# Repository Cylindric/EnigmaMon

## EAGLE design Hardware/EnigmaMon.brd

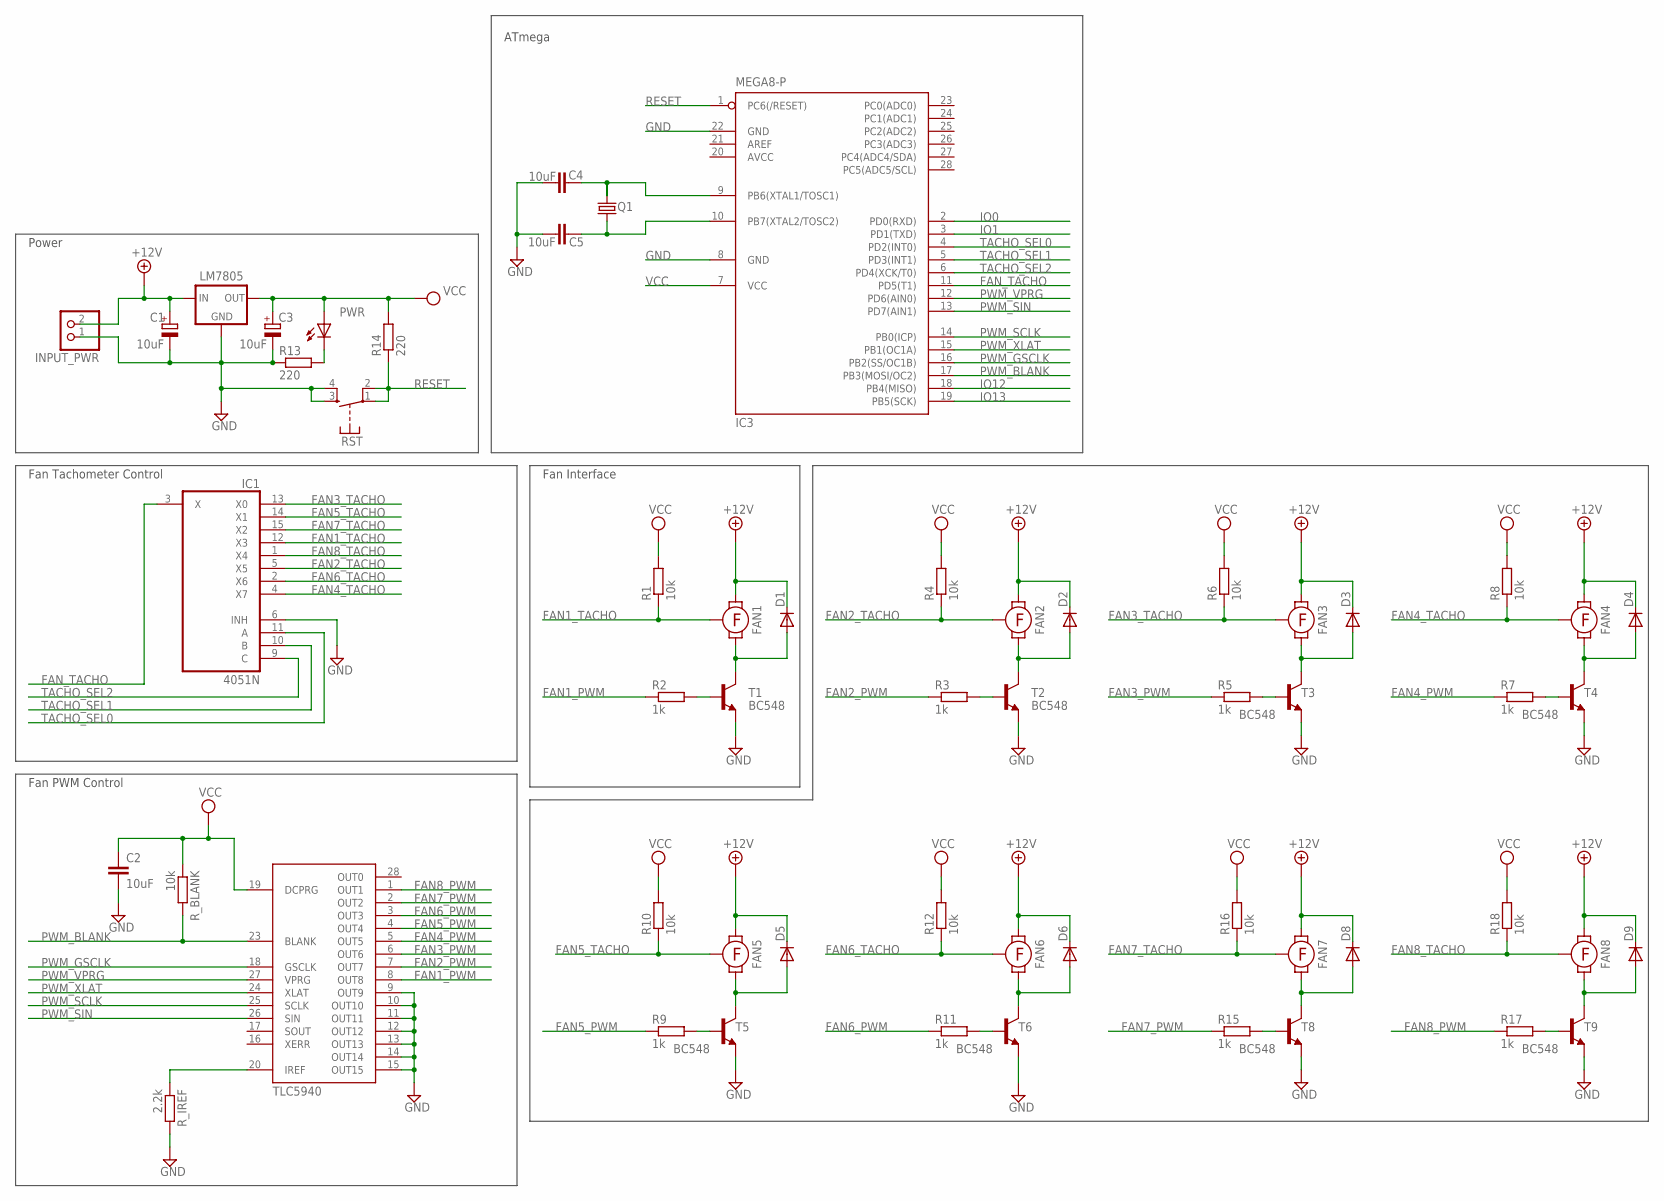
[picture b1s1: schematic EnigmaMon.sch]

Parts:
C1, C3: 10uF; E2,5-6
C2, C4, C5: 10uF; C025-025X050
D1, D2, D3, D4, D5, D6, D8, D9: DIODE-D-5; D-5
FAN1, FAN2, FAN3, FAN4, FAN5, FAN6, FAN7, FAN8: FAN; FAN_HEADER
IC1: 4051N; DIL16
IC2: TLC5940; DIL28-3
IC3: MEGA8-P; DIL28-3
INPUT_PWR: PINHD-1X2; 1X02
LM7805: 78XXL
PWR: LED3MM
Q1: CRYSTALHC49S; HC49/S
R1, R4, R6, R8, R10, R12, R16, R18: 10k; 0204/5
R2, R3, R5, R7, R9, R11, R15, R17: 1k; 0204/5
R13, R14: 220; 0204/7
RST: DTS6
R_BLANK: 10k; 0204/7
R_IREF: 2.2k; 0204/7
T1, T2, T3, T4, T5, T6, T8, T9: BC548; TO92

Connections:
+12V: C1.+, D1.C, D2.C, D3.C, D4.C, D5.C, D6.C, D8.C, D9.C, FAN1.VCC, FAN2.VCC, FAN3.VCC, FAN4.VCC, FAN5.VCC, FAN6.VCC, FAN7.VCC, FAN8.VCC, INPUT_PWR.2, LM7805.IN
AVCC: IC3.20 (AVCC)
FAN1_PWM: IC2.8 (OUT8), R2.1
FAN1_TACHO: FAN1.TACHO, IC1.12 (X3), R1.1
FAN2_PWM: IC2.7 (OUT7), R3.1
FAN2_TACHO: FAN2.TACHO, IC1.5 (X5), R4.1
FAN3_PWM: IC2.6 (OUT6), R5.1
FAN3_TACHO: FAN3.TACHO, IC1.13 (X0), R6.1
FAN4_PWM: IC2.5 (OUT5), R7.1
FAN4_TACHO: FAN4.TACHO, IC1.4 (X7), R8.1
FAN5_PWM: IC2.4 (OUT4), R9.1
FAN5_TACHO: FAN5.TACHO, IC1.14 (X1), R10.1
FAN6_PWM: IC2.3 (OUT3), R11.1
FAN6_TACHO: FAN6.TACHO, IC1.2 (X6), R12.1
FAN7_PWM: IC2.2 (OUT2), R15.1
FAN7_TACHO: FAN7.TACHO, IC1.15 (X2), R16.1
FAN8_PWM: IC2.1 (OUT1), R17.1
FAN8_TACHO: FAN8.TACHO, IC1.1 (X4), R18.1
FAN_TACHO: IC1.3 (X), IC3.11 (PD5(T1))
GND: C1.-, C2.2, C3.-, C4.1, C5.1, IC1.6 (INH), IC1.8 (GND), IC2.9 (OUT9), IC2.10 (OUT10), IC2.11 (OUT11), IC2.12 (OUT12), IC2.13 (OUT13), IC2.14 (OUT14), IC2.15 (OUT15), IC2.22 (GND), IC3.8 (GND), IC3.22 (GND), INPUT_PWR.1, LM7805.GND, R13.1, RST.3 (S), RST.4 (S), R_IREF.2, T1.1 (E), T2.1 (E), T3.1 (E), T4.1 (E), T5.1 (E), T6.1 (E), T8.1 (E), T9.1 (E)
IO0: IC3.2 (PD0(RXD))
IO1: IC3.3 (PD1(TXD))
IO12: IC3.18 (PB4(MISO))
IO13: IC3.19 (PB5(SCK))
unnamed: R3.2, T2.2 (B)
unnamed: R2.2, T1.2 (B)
unnamed: R5.2, T3.2 (B)
unnamed: R7.2, T4.2 (B)
unnamed: R9.2, T5.2 (B)
unnamed: R11.2, T6.2 (B)
unnamed: PWR.K (C), R13.2
unnamed: R15.2, T8.2 (B)
unnamed: R17.2, T9.2 (B)
unnamed: IC2.20 (IREF), R_IREF.1
unnamed: C4.2, IC3.9 (PB6(XTAL1/TOSC1)), Q1.2
unnamed: C5.2, IC3.10 (PB7(XTAL2/TOSC2)), Q1.1
unnamed: D2.A, FAN2.GND, T2.3 (C)
unnamed: D3.A, FAN3.GND, T3.3 (C)
unnamed: D4.A, FAN4.GND, T4.3 (C)
unnamed: D1.A, FAN1.GND, T1.3 (C)
unnamed: D9.A, FAN8.GND, T9.3 (C)
unnamed: D8.A, FAN7.GND, T8.3 (C)
unnamed: D6.A, FAN6.GND, T6.3 (C)
unnamed: D5.A, FAN5.GND, T5.3 (C)
PWM_BLANK: IC2.23 (BLANK), IC3.17 (PB3(MOSI/OC2)), R_BLANK.2
PWM_GSCLK: IC2.18 (GSCLK), IC3.16 (PB2(SS/OC1B))
PWM_SCLK: IC2.25 (SCLK), IC3.14 (PB0(ICP))
PWM_SIN: IC2.26 (SIN), IC3.13 (PD7(AIN1))
PWM_VPRG: IC2.27 (VPRG), IC3.12 (PD6(AIN0))
PWM_XLAT: IC2.24 (XLAT), IC3.15 (PB1(OC1A))
RESET: IC3.1 (PC6(/RESET)), R14.1, RST.1, RST.2
TACHO_SEL0: IC1.11 (A), IC3.4 (PD2(INT0))
TACHO_SEL1: IC1.10 (B), IC3.5 (PD3(INT1))
TACHO_SEL2: IC1.9 (C), IC3.6 (PD4(XCK/T0))
VCC: C2.1, C3.+, IC1.16 (VCC), IC2.19 (DCPRG), IC2.21 (VCC), IC3.7 (VCC), LM7805.OUT, PWR.A, R1.2, R4.2, R6.2, R8.2, R10.2, R12.2, R14.2, R16.2, R18.2, R_BLANK.1
VEE: IC1.7 (VEE)

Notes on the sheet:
Fan Tachometer Control
Power
Fan Interface
ATmega
Fan PWM Control

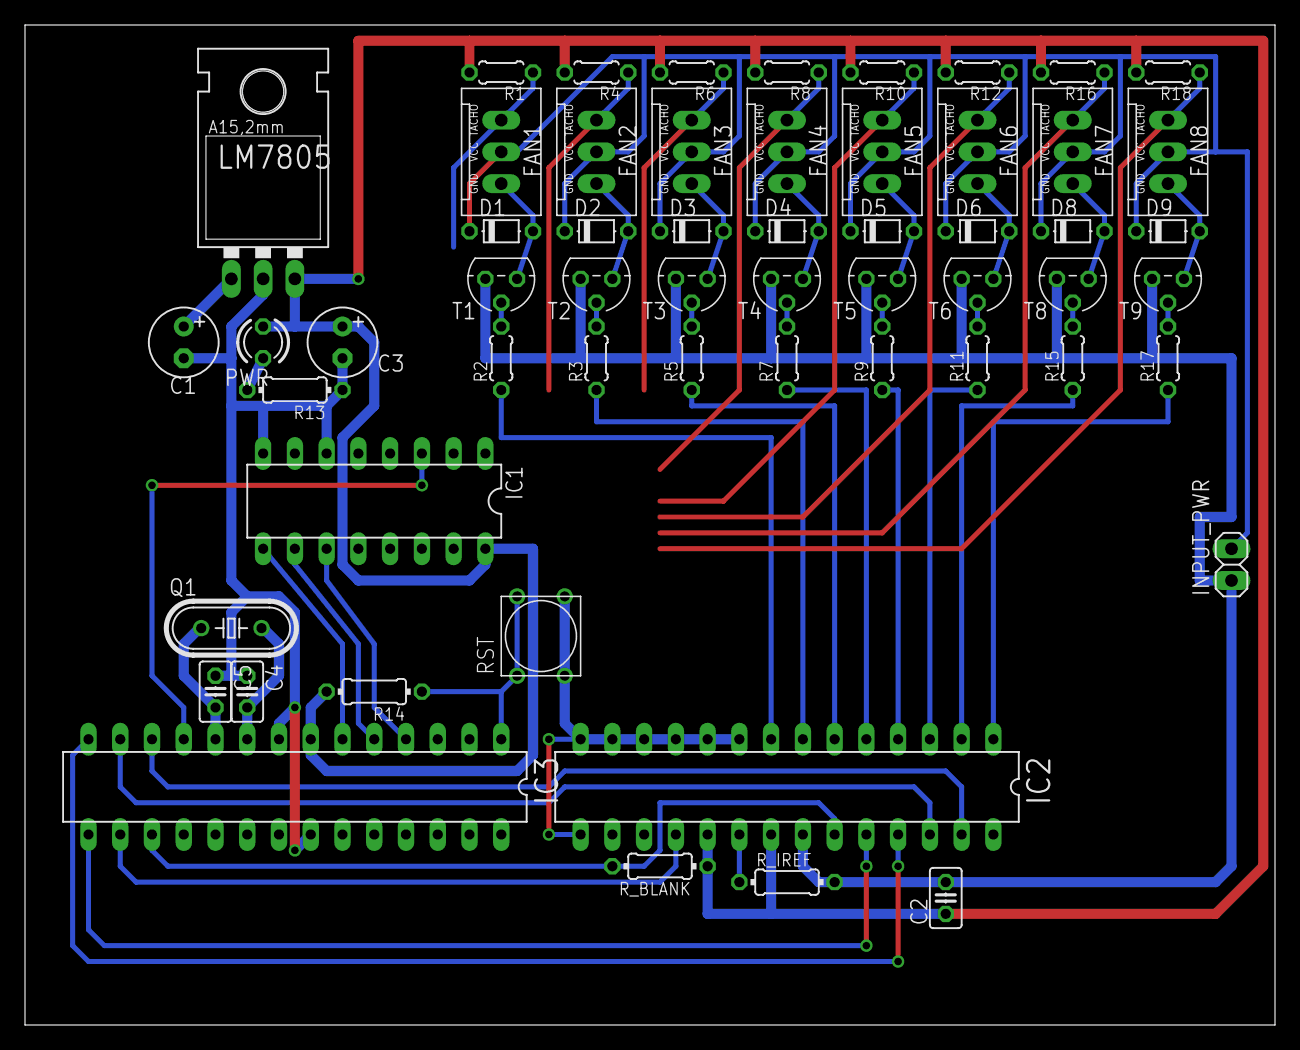
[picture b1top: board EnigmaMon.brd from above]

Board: 2 copper layers, 100.0 x 80.0 mm, 57 parts (0 on the bottom side), 50 nets.

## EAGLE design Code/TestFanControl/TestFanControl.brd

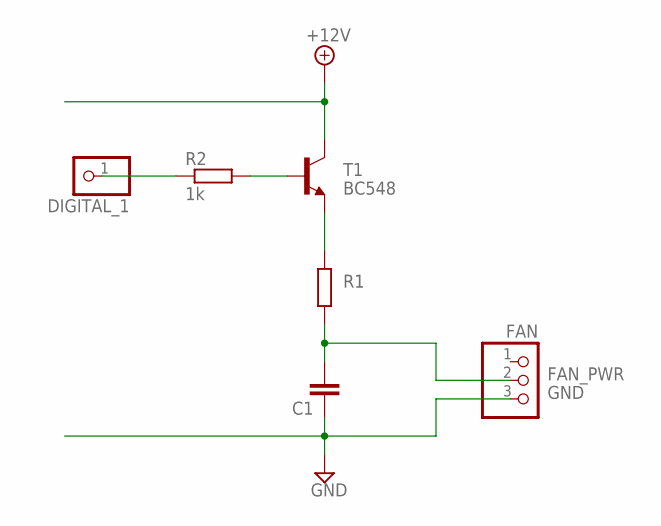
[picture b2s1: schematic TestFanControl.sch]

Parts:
C1: C-EU025-024X044; C025-024X044
DIGITAL_1: PINHD-1X1; 1X01
FAN: PINHD-1X3; 1X03
R1: R-EU_0204/7; 0204/7
R2: 1k; 0204/7
T1: BC548; TO92

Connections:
+12V: T1.3 (C)
FAN7_PWM: DIGITAL_1.1, R2.1
FAN_PWR: C1.2, FAN.2, R1.2
GND: C1.1, FAN.3
unnamed: R2.2, T1.2 (B)
unnamed: R1.1, T1.1 (E)

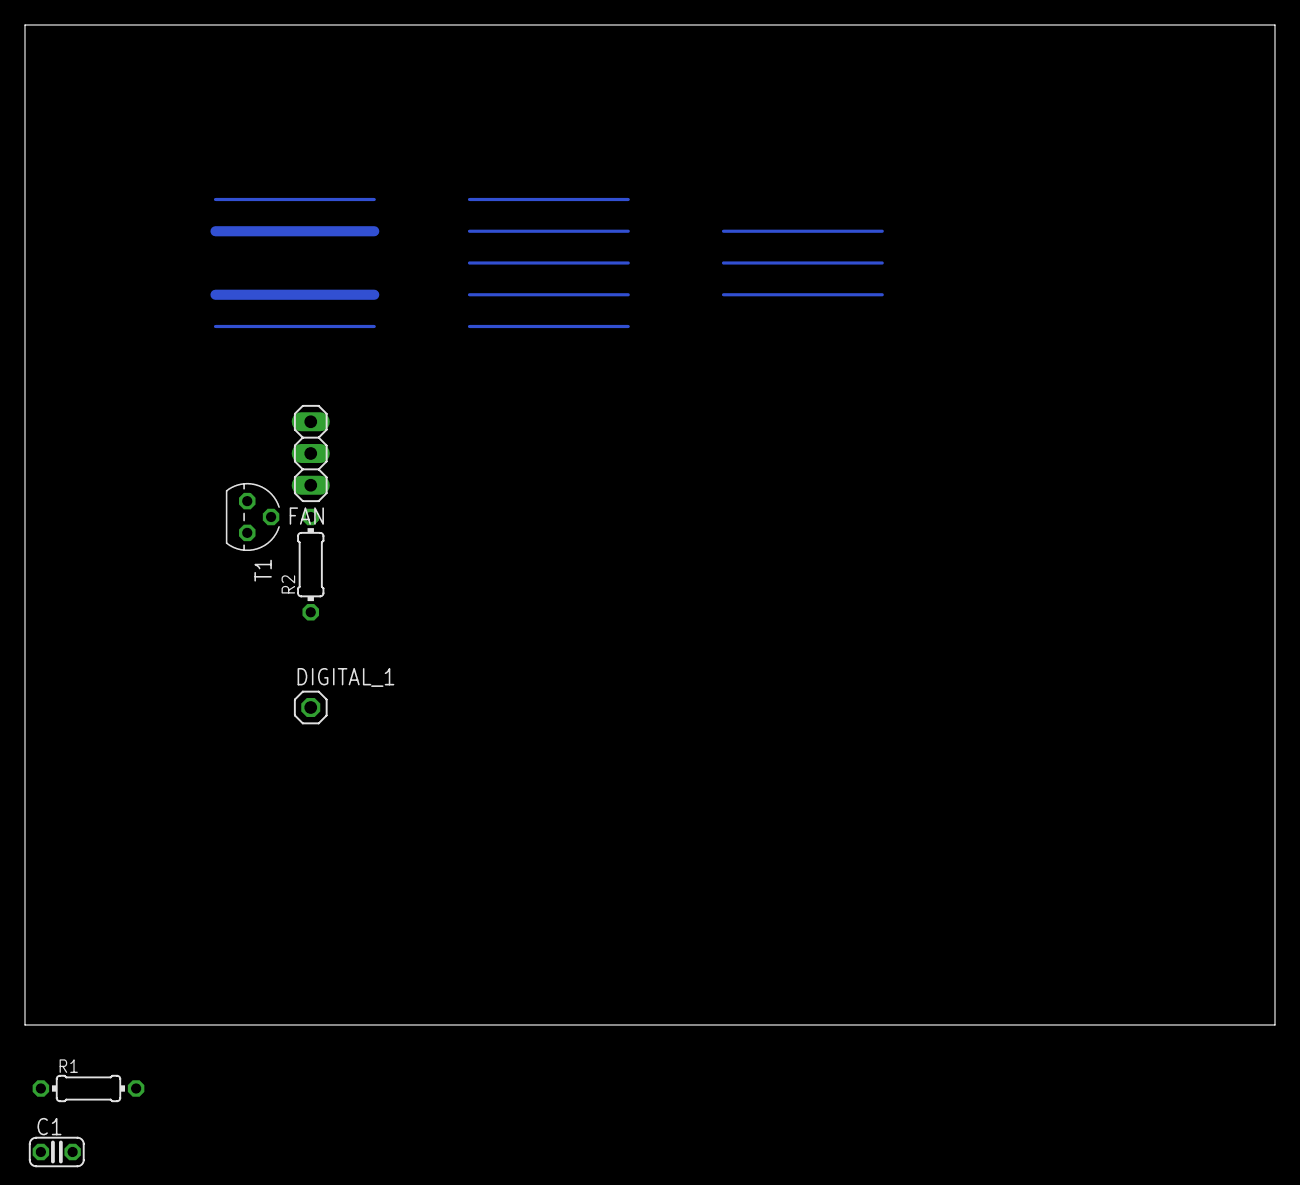
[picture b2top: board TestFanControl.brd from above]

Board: 2 copper layers, 100.0 x 80.0 mm, 6 parts (0 on the bottom side), 5 nets.

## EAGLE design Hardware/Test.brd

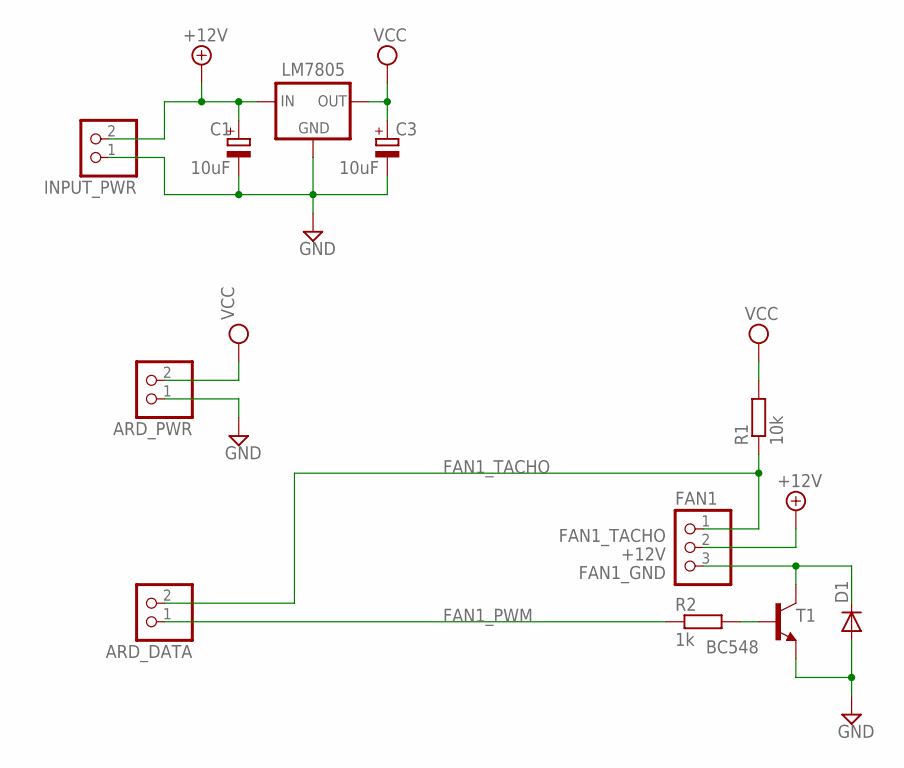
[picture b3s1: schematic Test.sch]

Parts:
ARD_DATA: PINHD-1X2; 1X02
ARD_PWR: PINHD-1X2; 1X02
C1, C3: 10uF; E2,5-6
D1: DIODE-D-7.5; D-7.5
FAN1: PINHD-1X3; 1X03
INPUT_PWR: PINHD-1X2; 1X02
LM7805: 78XXL
R1: 10k; 0207/10
R2: 1k; 0204/7
T1: BC548; TO92

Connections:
+12V: C1.+, FAN1.2, INPUT_PWR.2, LM7805.IN
FAN1_GND: D1.C, FAN1.3, T1.3 (C)
FAN1_PWM: ARD_DATA.1, R2.1
FAN1_TACHO: ARD_DATA.2, FAN1.1, R1.1
GND: ARD_PWR.1, C1.-, C3.-, D1.A, INPUT_PWR.1, LM7805.GND, T1.1 (E)
unnamed: R2.2, T1.2 (B)
VCC: ARD_PWR.2, C3.+, LM7805.OUT, R1.2

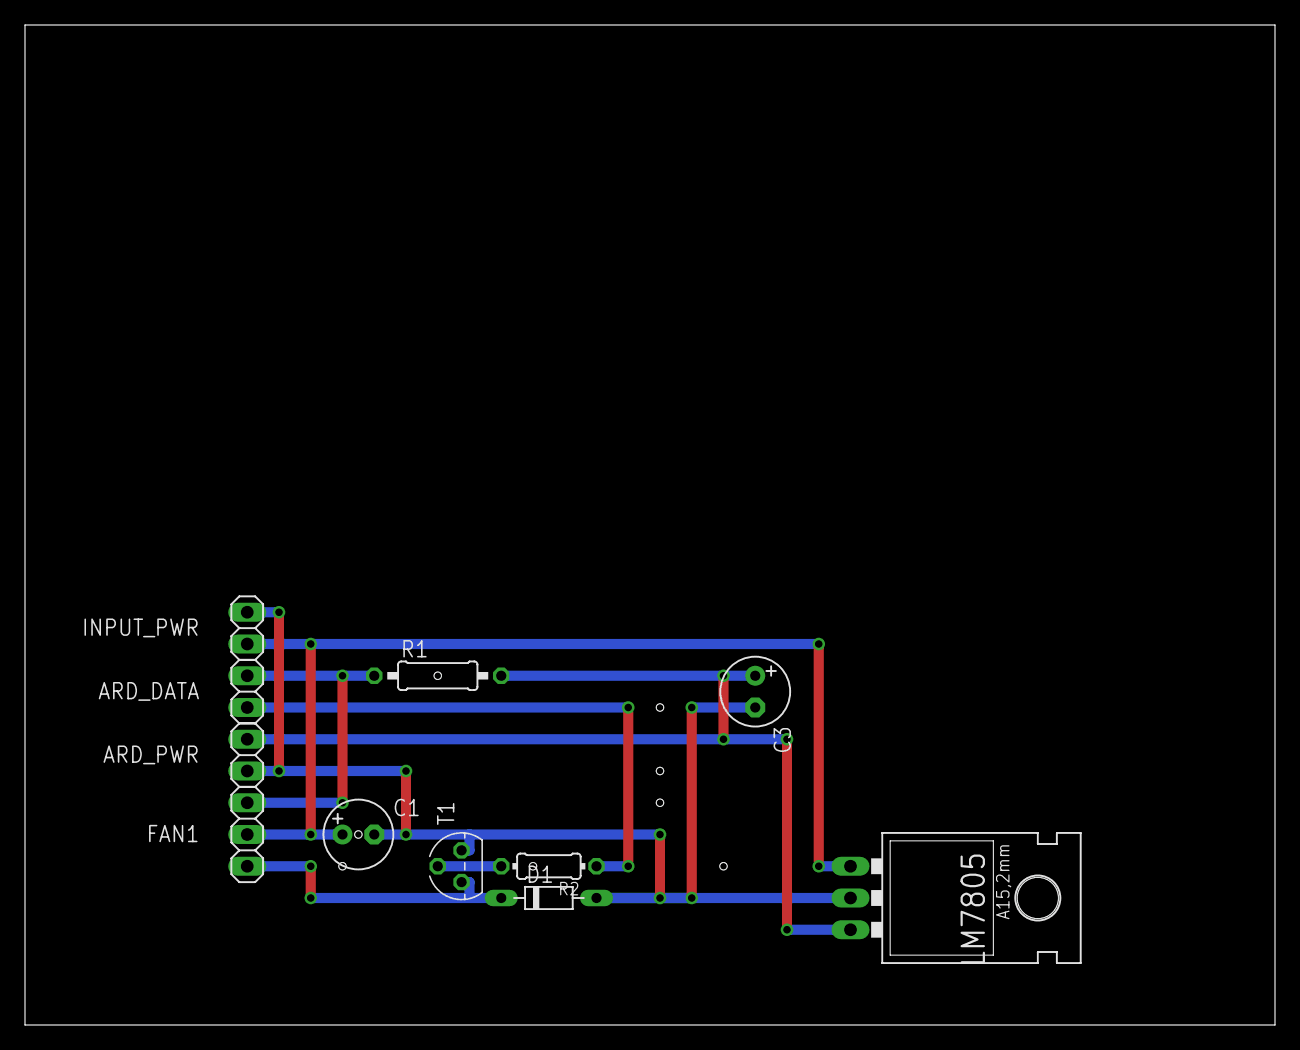
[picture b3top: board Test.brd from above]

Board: 2 copper layers, 100.0 x 80.0 mm, 11 parts (0 on the bottom side), 7 nets.

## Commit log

2011-06-26 Added initial display board files
2011-06-26 Updated Display diagram
2011-06-28 updated diagram
2011-06-28 updated projects
2011-06-28 Removed temp file
2011-06-28 Updated Display
2011-06-29 Created a draft sensor circuit
2011-07-05 Added some LCD design aids
2011-07-07 fixing capitalisation
2011-07-07 Removed obsolete display schematics
2011-07-11 Working on LCD - buggy Serial IO
2011-07-12 Updated tests for GLCD
2011-07-24 Updated docs and tests
2011-07-25 Initial schematics
2011-07-25 Adding a VRM for the LCD
2011-07-26 New schematics
2011-07-26 Added some Arduino connectors to the library
2011-07-27 Added an LCD interface board
2012-02-03 added fan test
2012-02-06 Tinkering with the wiring
2012-02-07 Added some interesting muxers
2012-02-07 Updated schematics
2012-02-07 Added VMR
2012-02-08 Fixed error with reset switch
2012-02-08 Couple of minor updates
2012-02-09 Added some test schematics
2012-02-10 Started wiring for on-board ATmega
2012-02-10 Added test for the fan tacho
2012-02-10 Some testing of tacho methods
2012-02-11 Testing
